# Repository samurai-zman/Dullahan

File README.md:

# Dullahan
A portable "Headless" modular multiport multitool, designed to emphasize adaptability for electronic measurements.

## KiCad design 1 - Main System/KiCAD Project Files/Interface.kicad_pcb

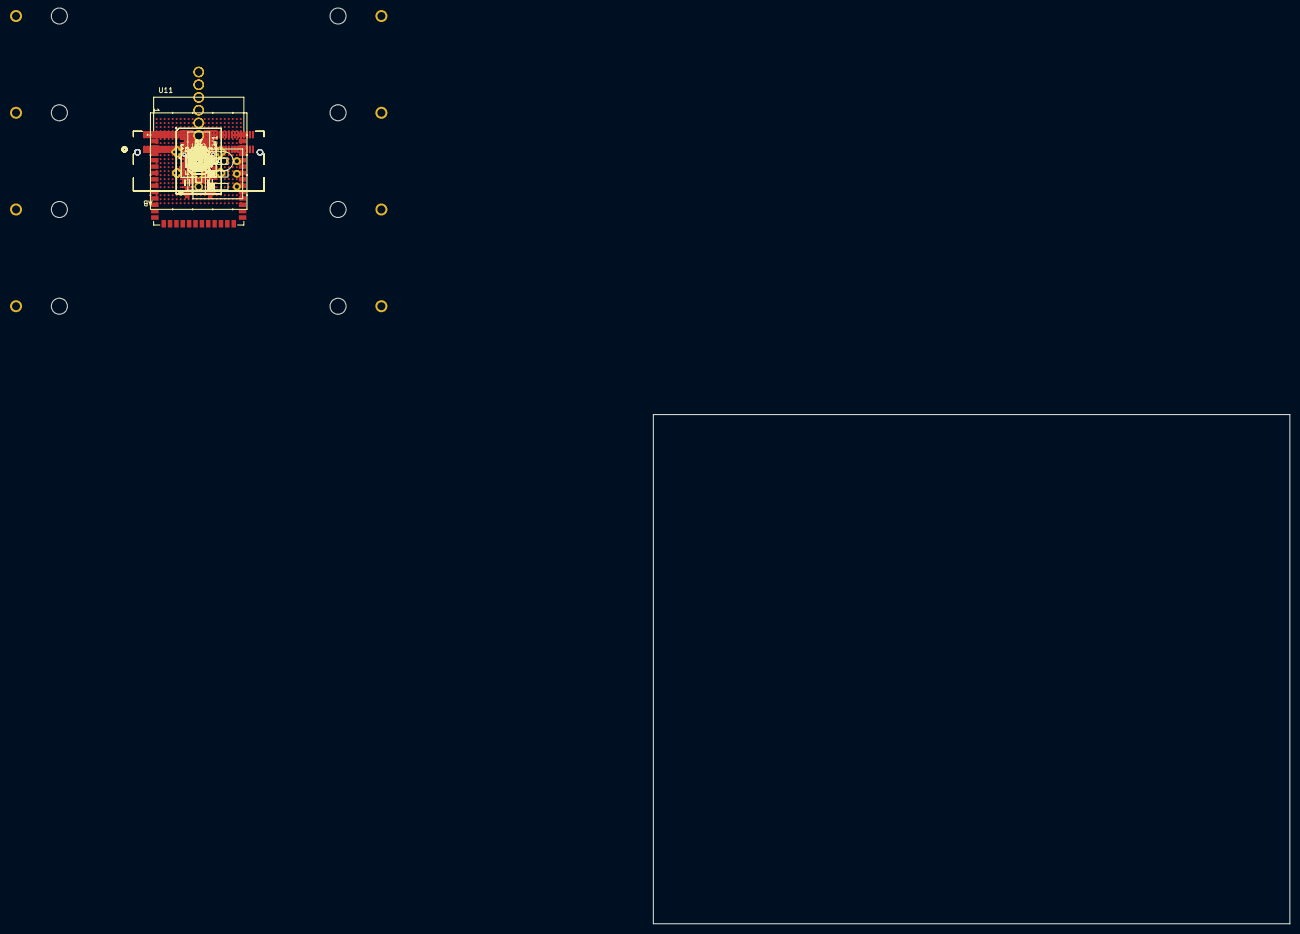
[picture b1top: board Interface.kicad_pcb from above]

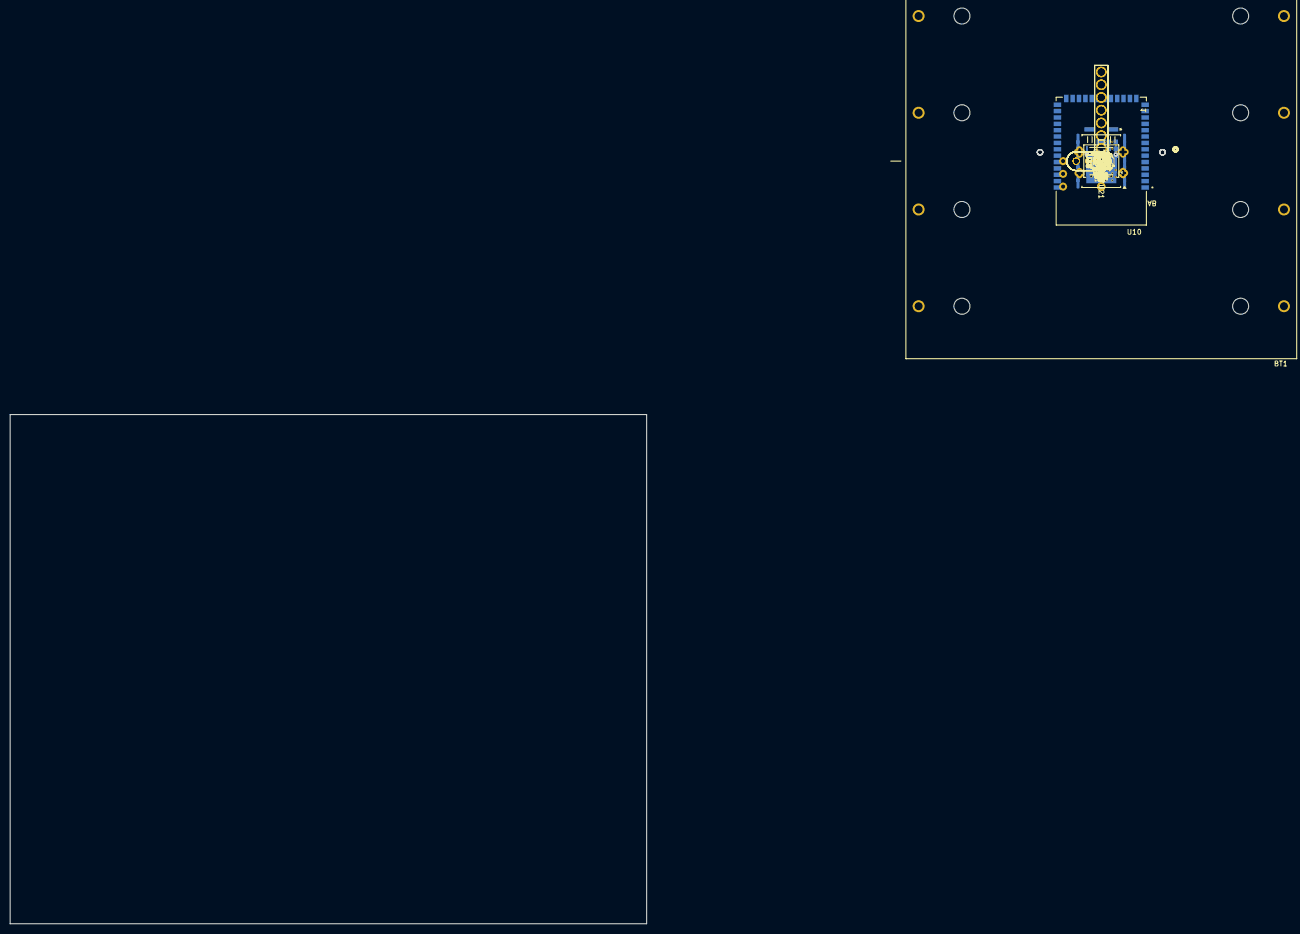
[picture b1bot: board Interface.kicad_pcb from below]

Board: 6 copper layers, 127.0 x 101.6 mm, 580 parts (177 on the bottom side), 365 nets.

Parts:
BT1: BK-18650-PC8; BAT_BK-18650-PC8
C1, C4, C5, C8, C10, C14, C15, C16, C17, C20, C23, C31, C152, C246, C253: 22uF; C_0805
C2, C3, C32, C35, C160, C162, C164, C166, C168, C249: 1uF; C_0805
C6, C7, C11, C12: 220nF; C_0603
C9, C13, C79, C80, C82, C84, C85, C88, C89, C92, C95, C98, C99, C110, C111, C112, C113, C114, C115, C116, C117, C124, C125, C126, C127, C128, C129, C130, C131, C137, C138, C139, C140, C141, C142, C144, C146: 470nF; C_0402
C18: 47pF; C_0805
C19: 18pF; C_0805
C21, C22, C24, C25, C73, C74, C75: 2.2uF; C_0805_2012Metric
C26, C28, C29, C30, C33, C34, C36, C37, C38, C39, C40, C41, C42, C47, C50, C53, C54, C102, C103, C149, C153, C154, C155, C157, C158, C169, C170, C171, C181, C182, C184, C248, C255: 10uF; C_0805
C27: 33pF; C_0805
C43, C44, C45, C46, C59, C60, C61, C62, C183, C240, C241, C245: 100nF; C_0402
C48, C49, C51, C52, C55, C56, C57, C58: 220pF; C_0805
C63, C64, C65, C66, C68, C72, C100, C151, C161, C163, C165, C167, C172, C173, C175, C250: 100nF; C_0805
C67, C69, C70, C71, C174, C176, C177, C178: 1nF; C_0402
C76: 330uF; C_0603
C77, C78, C81, C87, C91, C94, C97, C106, C107, C108, C109, C120, C121, C122, C123, C134, C135, C136, C145: 4.7uF; C_0402
C83, C96, C133, C143: 100uF; C_0603
C86, C90, C93, C104, C105, C118, C119, C132, C147, C148: 47uF; C_0603
C101, C150, C156, C159: 2.2uF; C_0402
C179, C180, C185, C186, C187, C188, C189, C190, C191, C192, C193, C194, C195, C196, C197, C198, C199, C200, C201, C202, C203, C204, C205, C206, C207, C208, C209, C210, C211, C212, C213, C214, C215, C216, C217, C218, C219, C220, C221, C222, C223, C224, C225, C226, C227, C228, C229, C230, C231, C232, C233, C234, C235, C236: 47nF; C_0402
C237, C239: 1uF; C_0402
C238, C242, C243, C244: 10uF; C_0402
C247, C251, C252, C254: 4.7uF; C_0805
D1, D54: PRTR5V0U2X; SOT-143R_Handsoldering
D2, D3, D4, D5, D6, D22, D23, D24, D25, D26, D27, D28, D29, D30, D31, D32, D33, D34, D35, D36, D37, D38, D39, D40, D41, D42, D43, D44, D45, D46, D47, D48, D49, D50, D52, D57, D58, D59, D60, D61, D62, D63, D64, D65, D66, D67: D; D_0805_2012Metric_Pad1.15x1.40mm_HandSolder
D7, D17, D18, D19: BAT60A; D_SOD-323
D8, D9, D10, D11, D12, D13, D14, D20, D21: Blue; LED_0603_1608Metric_Blue
D15: BSTAT; LED_0603
D16: BOK; LED_0603
D51, D53: Blue; D_0805
IC1, IC2, IC3, IC4: AP22966DC8-7; AP22966DC87
IC5: TMUXHS221FRSWR
IC6, IC7: MAX77857CEWB+; BGA35C40P7X5_283X203X69
IC8, IC9: IS43TR16640C-125JBL; BGA96C80P9X16_900X1300X120
J1, J2: Connector, USB-TYPE-C-16P; TYPE-C-SMD_HX-TYPE-C-16PIN
J3: PinSocket_01x03_P2.54mm_Vertical_SMD; PinSocket_1x03_P2.54mm_Vertical
J4, J7, J8, J9: G97R22312HR; CONN_G97R22xx2HR_AMP
J5: JTAGHDR_RPi; PinHeader_01x08_P2.54mm_Vertical_THT_D1.4mm
J6: JTAGHDR_FPGA; PinHeader_01x08_P2.54mm_Vertical_THT_D1.4mm
J17, J18: PinHeader_01x01_P2.54mm_Vertical_THT_D1mm
JP3, JP4: Jumper_2_Bridged; Jumper_2_NC_Trace
L1, L21: 1.5uH; Inductor_4.7x4.7mm
L2, L3, L4, L5: 1.0uH; 0805
L10: 30 Ohm; C_0603_1608Metric
L11: 120 Ohm; C_0603_1608Metric
L12: 0.47uH; Inductor_4.7x4.7mm
Q4: 2N7002; SOT-23
Q5, Q6: T2N7002AK; SOT-23
R1, R2, R4, R8, R37, R38, R42, R43, R44, R82, R83, R84, R85, R86, R87, R115, R116: 10kΩ; R_0402
R3, R6: 510kΩ; R_0402
R5: 200Ω; R_0402
R7: 422Ω; R_0402
R9, R11: 5.1kΩ; R_0805
R10, R18, R35: 1kΩ; R_0805
R12: 5.1Ω; R_0805
R13, R14: 2.2kΩ; R_0805
R15, R16, R119: 10kΩ; R_0805
R17, R19, R23, R59, R124: 12kΩ; R_0402
R20: 47kΩ; R_0805
R21, R22, R25, R28, R29, R30, R45, R118: 330Ω; R_0805
R24, R47, R54, R55, R57, R103, R104, R105: 4.7kΩ; R_0402
R26, R46, R102: 100Ω; R_0402
R27, R39, R40, R41, R71, R74, R80, R81, R98: 0Ω; R_0402
R31, R33, R36: 20kΩ; R_0805
R32: 24kΩ; R_0805
R34: 68kΩ; R_0805
R48, R49, R50, R51, R52, R53, R66, R67, R68, R70, R73, R99, R100, R122: 1kΩ; R_0402
R56: 24.9Ω; R_0402
R58, R77: 510Ω; R_0402
R60, R89, R91, R93, R95, R97, R123: 100kΩ; R_0402
R61, R62, R63, R64, R65, R69, R72: 20kΩ; R_0402
R75, R76, R78, R79: 22Ω; R_0402
R88, R90, R92, R94, R96: 1MΩ; R_0402
R101, R106, R107, R108, R109, R110, R111, R112, R113: 49.9Ω; R_0402
R114, R121: 240Ω; R_0402
R117: 10kΩ; C_0805
R120: 330Ω; C_0805
RV1, RV2, RV3, RV4: CG0402MLU-3.3G; VARC1005X41N
S1, S2, S3, S4, S39, S41: Tactile Button, 160gf; SW_TS-1088-AR02016
S5, S6, S7, S8, S9, S10, S11, S12, S13, S14, S15, S16, S17, S18, S19, S20, S21, S22, S23, S24, S25, S26, S27, S28, S29, S30, S31, S32, S33, S34, S35, S36, S37, S38, S40, S45, S46, S47, S48, S49, S50, S51, S52, S53, S54, S55: Tactile Button, 160gf; SW-SMD_4P-L5.1-W5.1-P3.70-LS6.5-TL-2
SW1: SW_DIP_x03; SW_DIP_SPSTx03_Slide_9.78x9.8mm_W7.62mm_P2.54mm
SW2: SPDT_Slide_PTH_11.6x4.0mm; Slide_SPDT_PTH_11.6x4.0mm
TH1: Thermistor_NTC; R_1206
TP6, TP7: TestPoint_Alt; TestPoint-1.0mm
U1: MAX20029BATIA/V+; 21-0140AK_T2855&plus_5_MXM-L
U2, U4, U5, U6, U8, U9: LD39200PU33R; SON95P300X300X100-7N
U3, U18, U30: STTH1002CB-TR; DPAK_STM-L
U7: ADS7830; TSSOP-16_4.4x5mm_P0.65mm
U10, U11: ESP32-S3-WROOM-1-N4; XCVR_ESP32-S3-WROOM-1-N4
U12, U13, U14, U15, U16, U35, U36, U37: ACS711xEXLT-15AB; Allegro_QFN-12-10-1EP_3x3mm_P0.5mm
U17: XC7Z020-1CLG484C; CLG484_XIL-L
U19: MAX77789EWX+T; 21-100639_W362K2&plus_1_ADI-L
U20, U22, U24, U26, U28: TPS2592xx; VSON-10-1EP_3x3mm_P0.5mm_EP1.65x2.4mm_ThermalVias
U21: PCF8574AT; SOIC-16W_7.5x10.3mm_P1.27mm
U23, U29, U31, U32, U33, U34, U38, U39, U40: DSS1NB32A223Q91A; DSS1NB32A223Q91A_MUR
U25: BD3539FVM-TR; MSOP8_ROM
Y1: ASDMB-xxxMHz; Oscillator_SMD_Abracon_ASDMB-4Pin_2.5x2.0mm

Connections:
+0V675: C203.1, C204.1, C205.1, C206.1, C207.1, C208.1, C209.1, C210.1, C211.1, C212.1, R101.1, R106.1, R107.1, R108.1, R109.1, R110.1, R111.1, R112.1, R113.1
+0V675_REF: U17.H7 (PS_DDR_VREF0_502), U17.P7 (PS_DDR_VREF1_502)
+1V0FPGA: C4.1, C5.1, C16.1, C76.1, C77.1, C78.1, C79.1, C80.1, C81.1, C82.1, C83.1, C84.1, C85.1, C133.1, C135.1, C137.1, C139.1, C141.1, L2.1, U1.28 (OUTS1), U17.G8 (VCCPINT), U17.H9 (VCCPINT), U17.H11 (VCCBRAM), U17.J8 (VCCPINT), U17.J10 (VCCBRAM), U17.J12 (VCCINT), U17.J14 (VCCINT), U17.K13 (VCCINT), U17.L8 (VCCPINT), U17.L14 (VCCINT), U17.M13 (VCCINT), U17.N8 (VCCPINT), U17.N14 (VCCINT), U17.P13 (VCCINT), U17.R8 (VCCPINT), U17.R14 (VCCINT)
+1V8FPGA: C19.1, C44.1, C86.1, C87.1, C88.1, C89.1, C93.1, C94.1, C95.1, C99.1, C143.1, C145.1, C146.1, C148.1, L11.2, R17.1, R19.2, R23.2, R36.1, U17.A10 (VCCO_MIO1_501), U17.B13 (VCCO_MIO1_501), U17.D9 (VCCO_MIO1_501), U17.E12 (VCCO_MIO1_501), U17.G9 (VCCBATT_0), U17.K9 (VCCPAUX), U17.K11 (VCCADC_0), U17.L10 (VCCAUX), U17.M9 (VCCPAUX), U17.N10 (VCCAUX), U17.P9 (VCCPAUX), U17.P11 (VCCAUX), U17.R10 (VCCAUX), U17.T9 (VCCPAUX)
+1V35FPGA: C18.1, C104.1, C106.1, C108.1, C110.1, C112.1, C114.1, C116.1, C179.1, C180.1, C185.1, C186.1, C187.1, C188.1, C189.1, C190.1, C191.1, C192.1, C193.1, C194.1, C195.1, C196.1, C197.1, C198.1, C199.1, C200.1, C201.1, C202.1, C214.1, C215.1, C216.1, C217.1, C218.1, C219.1, C220.1, C221.1, C222.1, C223.1, C224.1, C225.1, C226.1, C227.1, C228.1, C229.1, C230.1, C231.1, C232.1, C233.1, C234.1, C236.1, IC8.A1 (VDDQ_1), IC8.A8 (VDDQ_2), IC8.B2 (VDD_1), IC8.C1 (VDDQ_3), IC8.C9 (VDDQ_4), IC8.D2 (VDDQ_5), IC8.D9 (VDD_2), IC8.E9 (VDDQ_6), IC8.F1 (VDDQ_7), IC8.G7 (VDD_3), IC8.H1 (VREFDQ), IC8.H2 (VDDQ_8), IC8.H9 (VDDQ_9), IC8.K2 (VDD_4), IC8.K8 (VDD_5), IC8.N1 (VDD_6), IC8.N9 (VDD_7), IC8.R1 (VDD_8), IC8.R9 (VDD_9), IC9.A1 (VDDQ_1), IC9.A8 (VDDQ_2), IC9.B2 (VDD_1), IC9.C1 (VDDQ_3), IC9.C9 (VDDQ_4), IC9.D2 (VDDQ_5), IC9.D9 (VDD_2), IC9.E9 (VDDQ_6), IC9.F1 (VDDQ_7), IC9.G7 (VDD_3), IC9.H1 (VREFDQ), IC9.H2 (VDDQ_8), IC9.H9 (VDDQ_9), IC9.K2 (VDD_4), IC9.K8 (VDD_5), IC9.N1 (VDD_6), IC9.N9 (VDD_7), IC9.R1 (VDD_8), IC9.R9 (VDD_9), R26.2, R31.1, R46.2, R122.1, U17.E2 (VCCO_DDR_502), U17.F5 (VCCO_DDR_502), U17.H1 (VCCO_DDR_502), U17.J4 (VCCO_DDR_502), U17.K7 (VCCO_DDR_502), U17.M3 (VCCO_DDR_502), U17.N6 (VCCO_DDR_502), U17.R2 (VCCO_DDR_502), U17.V1 (VCCO_DDR_502)
+3V3FPGA: C27.1, C90.1, C91.1, C92.1, C105.1, C107.1, C109.1, C111.1, C113.1, C115.1, C117.1, C118.1, C119.1, C120.1, C121.1, C122.1, C123.1, C124.1, C125.1, C126.1, C127.1, C128.1, C129.1, C130.1, C131.1, C132.1, C134.1, C136.1, C138.1, C140.1, C142.1, C144.1, C147.1, J6.8, R21.1, R33.1, R54.2, R55.2, R57.2, R58.1, R62.2, R71.1, R74.2, R77.1, R103.2, R104.2, R105.2, SW1.4, SW1.5, SW1.6, U17.A20 (VCCO_35), U17.AA10 (VCCO_13), U17.AA20 (VCCO_33), U17.AB3 (VCCO_13), U17.AB13 (VCCO_33), U17.B3 (VCCO_MIO0_500), U17.C6 (VCCO_MIO0_500), U17.C16 (VCCO_35), U17.D19 (VCCO_35), U17.E22 (VCCO_35), U17.F15 (VCCO_35), U17.G18 (VCCO_35), U17.H21 (VCCO_35), U17.K17 (VCCO_34), U17.L20 (VCCO_34), U17.N16 (VCCO_34), U17.P19 (VCCO_34), U17.R12 (VCCO_0), U17.R22 (VCCO_34), U17.T5 (VCCO_13), U17.T7 (RSVDVCC1), U17.T8 (RSVDVCC2), U17.T10 (RSVDVCC3), U17.T13 (CFGBVS_0), U17.T15 (VCCO_34), U17.U8 (VCCO_13), U17.U18 (VCCO_33), U17.V11 (VCCO_13), U17.V21 (VCCO_33), U17.W4 (VCCO_13), U17.W14 (VCCO_33), U17.Y7 (VCCO_13), U17.Y17 (VCCO_33), Y1.4 (VDD)
+3V3JTAG: C62.1, C184.1, C237.1, C238.1, J5.8, R45.1, R115.1, R116.2, U8.1 (OUT), U8.2 (SENSE), U10.2 (3V3)
+3V3KEB: C63.1, C248.1, C249.1, C255.1, J17.1 (Pin_1_1), R117.1, R120.1, U9.1 (OUT), U9.2 (SENSE), U11.2 (3V3)
+5VB: R48.2, R49.2, R50.2, R51.2, R52.2, R53.2, R99.2, R100.2
+5VM: C14.1, C15.1, C64.1, C65.1, C66.1, C68.1, C72.1, C172.1, C173.1, C175.1, C242.1, C244.1, D7.2 (A), D17.2 (A), D18.2 (A), D19.2 (A), IC7.D4 (OUT_1), IC7.E1 (FB), IC7.E4 (OUT_2), IC7.E5 (OUT_3), IC7.E6 (OUT_4), R12.2, R13.1, R14.1, R15.1, R16.1, R119.1, U12.10 (VCC), U13.10 (VCC), U14.10 (VCC), U15.10 (VCC), U16.10 (VCC), U21.16 (VDD), U35.10 (VCC), U36.10 (VCC), U37.10 (VCC)
+VIOB: C150.1, R2.1, R82.1, R83.1, U19.F4 (VDD)
+VIOM: C13.1, IC7.A2 (VIO), R8.1, R86.1, R87.1
+VIOPI: C9.1, IC6.A2 (VIO), R4.1, R84.1, R85.1
/3V3 Regulator Supplies/3M1: U37.1 (IP+), U40.3
/3V3 Regulator Supplies/3M2: U36.1 (IP+), U39.3
/3V3 Regulator Supplies/3M3: U35.1 (IP+), U38.3
/3V3 Regulator Supplies/3M4: U16.1 (IP+), U34.3
/3V3 Regulator Supplies/5M1: U15.1 (IP+), U33.3
/3V3 Regulator Supplies/5M2: U14.1 (IP+), U32.3
/3V3 Regulator Supplies/5M3: U13.1 (IP+), U31.3
/3V3 Regulator Supplies/5M4: U12.1 (IP+), U29.3
/3V3 Regulator Supplies/5VM1: C53.1, C160.1, C171.1, IC1.1 (VIN1), IC1.5 (VIN2), R98.1, U20.6 (OUT), U20.7 (OUT), U20.8 (OUT)
/3V3 Regulator Supplies/5VM2: C50.1, C164.1, C170.1, IC2.1 (VIN1), IC2.5 (VIN2), R81.1, U24.6 (OUT), U24.7 (OUT), U24.8 (OUT)
/3V3 Regulator Supplies/5VM3: C47.1, C166.1, C169.1, IC3.1 (VIN1), IC3.5 (VIN2), R80.1, U26.6 (OUT), U26.7 (OUT), U26.8 (OUT)
/3V3 Regulator Supplies/5VM4: C36.1, C54.1, C168.1, IC4.1 (VIN1), IC4.5 (VIN2), R27.1, U28.6 (OUT), U28.7 (OUT), U28.8 (OUT)
/3V3 Regulator Supplies/M1_3VEN: IC1.4 (EN2), U21.5 (P1)
/3V3 Regulator Supplies/M1_5VEN: IC1.2 (EN1), U21.11 (P6)
/3V3 Regulator Supplies/M1_PG: U2.4 (PG), U10.26 (IO45)
/3V3 Regulator Supplies/M2_3VEN: IC2.4 (EN2), U21.7 (P3)
/3V3 Regulator Supplies/M2_5VEN: IC2.2 (EN1), U21.9 (P4)
/3V3 Regulator Supplies/M2_PG: U4.4 (PG), U10.16 (IO46)
/3V3 Regulator Supplies/M3_3VEN: IC3.4 (EN2), U21.10 (P5)
/3V3 Regulator Supplies/M3_5VEN: IC3.2 (EN1), U21.6 (P2)
/3V3 Regulator Supplies/M3_PG: U5.4 (PG), U10.24 (IO47)
/3V3 Regulator Supplies/M4_3VEN: IC4.4 (EN2), U21.12 (P7)
/3V3 Regulator Supplies/M4_5VEN: IC4.2 (EN1), U21.4 (P0)
/3V3 Regulator Supplies/M4_PG: U6.4 (PG), U10.25 (IO48)
/5V Boost Supplies/5VM_INT: IC7.C2 (POKB/_INTB), R87.2, R119.2, U10.23 (IO21), U21.13 (~INT)
/5V Boost Supplies/5VM_SCL: IC7.A1 (SCL), R14.2, R16.2, R86.2, U7.14 (SCL), U10.11 (IO18), U21.15 (SDA)
/5V Boost Supplies/5VM_SDA: IC7.B1 (SDA), R8.2, R13.2, R15.2, U7.15 (SDA), U10.10 (IO17), U21.14 (SCL)
/5V Boost Supplies/5VP_INT: IC6.C2 (POKB/_INTB), R83.2, R84.2, U10.30 (IO37), U19.B1 (INTB)
/5V Boost Supplies/5VP_SCL: IC6.A1 (SCL), R82.2, R85.2, U10.34 (IO41), U19.D1 (SCL)
/5V Boost Supplies/5VP_SDA: IC6.B1 (SDA), R2.2, R4.2, U10.33 (IO40), U19.C1 (SDA)
/FPGA Power Distro/+0V674: C246.1, C247.1, U25.3 (VTTS), U25.8 (VTT)
/FPGA Power Distro/+0V674_REF: C251.1, U25.4 (VREF)
/FPGA Power Distro/FPGA_PG: C75.2, Q4.1 (G), R44.2, R124.1, U1.23 (PG4)
/FPGA/FPGA CFG and PWR/BM1: R65.1, R67.1, SW1.1
/FPGA/FPGA CFG and PWR/BM2: R64.1, R68.1, SW1.2
/FPGA/FPGA CFG and PWR/BM3: R63.1, R66.1, SW1.3
/FPGA/FPGA CFG and PWR/CLK: R56.1, Y1.3 (Out)
/FPGA/FPGA CFG and PWR/DONE: Q6.1 (G), U17.T12 (DONE_0)
/FPGA/FPGA CFG and PWR/FPGA_TCK: J6.3, R79.1, R104.1, RV1.1
/FPGA/FPGA CFG and PWR/FPGA_TDI: J6.1, R75.1, R103.1, RV4.1
/FPGA/FPGA CFG and PWR/FPGA_TDO: J6.2, R76.1, RV3.1
/FPGA/FPGA CFG and PWR/FPGA_TMS: J6.4, R78.1, R105.1, RV2.1
/FPGA/FPGA CFG and PWR/PS_LED: R59.1, R60.2, U17.G6 (PS_MIO0_500)
/FPGA/FPGA CFG and PWR/QBOO_CLK_BM4: R72.2, U17.A4 (PS_MIO6_500)
/FPGA/FPGA CFG and PWR/QBOO_D0_BM3: R69.2, U17.A2 (PS_MIO2_500)
/FPGA/FPGA CFG and PWR/QBOO_D1_BM1: R65.2, U17.F6 (PS_MIO3_500)
/FPGA/FPGA CFG and PWR/QBOO_D2_BM2: R64.2, U17.E4 (PS_MIO4_500)
/FPGA/FPGA CFG and PWR/QBOO_D3_BM0: R63.2, U17.A3 (PS_MIO5_500)
/FPGA/FPGA CFG and PWR/QBOO_VM0: R61.2, U17.D5 (PS_MIO7_500)
/FPGA/FPGA CFG and PWR/QBOO_VM1: R62.1, U17.E5 (PS_MIO8_500)
/FPGA/FPGA CFG and PWR/nINIT: R55.1, U17.T14 (INIT_B_0)
/FPGA/FPGA CFG and PWR/nPROGRAM: R54.1, S1.2 (B), U17.T11 (PROGRAM_B_0)
/FPGA/FPGA CFG and PWR/nSRST: C43.1, J6.5, R17.2, S3.2 (B), U17.C9 (PS_SRST_B_501)
/FPGA/FPGA DDR/DDR_A0: IC8.N3 (A0), IC9.N3 (A0), U17.M4 (PS_DDR_A0_502)
/FPGA/FPGA DDR/DDR_A1: IC8.P7 (A1), IC9.P7 (A1), U17.M5 (PS_DDR_A1_502)
/FPGA/FPGA DDR/DDR_A2: IC8.P3 (A2), IC9.P3 (A2), U17.K4 (PS_DDR_A2_502)
/FPGA/FPGA DDR/DDR_A3: IC8.N2 (A3), IC9.N2 (A3), U17.L4 (PS_DDR_A3_502)
/FPGA/FPGA DDR/DDR_A4: IC8.P8 (A4), IC9.P8 (A4), U17.K6 (PS_DDR_A4_502)
/FPGA/FPGA DDR/DDR_A5: IC8.P2 (A5), IC9.P2 (A5), U17.K5 (PS_DDR_A5_502)
/FPGA/FPGA DDR/DDR_A6: IC8.R8 (A6), IC9.R8 (A6), U17.J7 (PS_DDR_A6_502)
/FPGA/FPGA DDR/DDR_A7: IC8.R2 (A7), IC9.R2 (A7), U17.J6 (PS_DDR_A7_502)
/FPGA/FPGA DDR/DDR_A8: IC8.T8 (A8), IC9.T8 (A8), U17.J5 (PS_DDR_A8_502)
/FPGA/FPGA DDR/DDR_A9: IC8.R3 (A9), IC9.R3 (A9), U17.H5 (PS_DDR_A9_502)
/FPGA/FPGA DDR/DDR_A10: IC8.L7 (A10/AP), IC9.L7 (A10/AP), U17.J3 (PS_DDR_A10_502)
/FPGA/FPGA DDR/DDR_A11: IC8.R7 (A11), IC9.R7 (A11), U17.G5 (PS_DDR_A11_502)
/FPGA/FPGA DDR/DDR_A12: IC8.N7 (A12/BC#), IC9.N7 (A12/BC#), U17.H4 (PS_DDR_A12_502)
/FPGA/FPGA DDR/DDR_A13: IC8.T3 (NC(A13)), IC9.T3 (NC(A13)), U17.F4 (PS_DDR_A13_502)
/FPGA/FPGA DDR/DDR_A14: IC8.T7 (NC(A14)), IC9.T7 (NC(A14)), U17.G4 (PS_DDR_A14_502)
/FPGA/FPGA DDR/DDR_BA0: IC8.M2 (BA0), IC9.M2 (BA0), R111.2, U17.L7 (PS_DDR_BA0_502)
/FPGA/FPGA DDR/DDR_BA1: IC8.N8 (BA1), IC9.N8 (BA1), R112.2, U17.L6 (PS_DDR_BA1_502)
/FPGA/FPGA DDR/DDR_BA2: IC8.M3 (BA2), IC9.M3 (BA2), R113.2, U17.M6 (PS_DDR_BA2_502)
/FPGA/FPGA DDR/DDR_CAS: IC8.K3 (CAS#), IC9.K3 (CAS#), R108.2, U17.P3 (PS_DDR_CAS_B_502)
/FPGA/FPGA DDR/DDR_CKE: IC8.K9 (CKE), IC9.K9 (CKE), R106.2, U17.V3 (PS_DDR_CKE_502)
/FPGA/FPGA DDR/DDR_CKN: IC8.K7 (CK#), IC9.K7 (CK#), R102.1, U17.N5 (PS_DDR_CKN_502)
/FPGA/FPGA DDR/DDR_CKP: IC8.J7 (CK), IC9.J7 (CK), R102.2, U17.N4 (PS_DDR_CKP_502)
/FPGA/FPGA DDR/DDR_CS: IC8.L2 (CS#), IC9.L2 (CS#), R107.2, U17.P6 (PS_DDR_CS_B_502)
/FPGA/FPGA DDR/DDR_DM0: IC8.D3 (DMU), IC9.D3 (DMU), U17.B1 (PS_DDR_DM0_502)
/FPGA/FPGA DDR/DDR_DM1: IC8.E7 (DML), IC9.E7 (DML), U17.H3 (PS_DDR_DM1_502)
/FPGA/FPGA DDR/DDR_ODT: IC8.K1 (ODT), IC9.K1 (ODT), R101.2, U17.P5 (PS_DDR_ODT_502)
/FPGA/FPGA DDR/DDR_RAS: IC8.J3 (RAS#), IC9.J3 (RAS#), R109.2, U17.R5 (PS_DDR_RAS_B_502)
/FPGA/FPGA DDR/DDR_WE: IC8.L3 (WE#), IC9.L3 (WE#), R110.2, U17.R4 (PS_DDR_WE_B_502)
/FPGA/FPGA DDR/DDR_nRST: IC8.T2 (RESET#), IC9.T2 (RESET#), R47.1, U17.F3 (PS_DDR_DRST_B_502)
/FPGA/FPGA DDR/DQSL_N: IC8.G3 (DQSL#), IC9.G3 (DQSL#), U17.J2 (PS_DDR_DQS_N1_502)
/FPGA/FPGA DDR/DQSL_P: IC8.F3 (DQSL), IC9.F3 (DQSL), U17.H2 (PS_DDR_DQS_P1_502)
/FPGA/FPGA DDR/DQSU_N: IC8.B7 (DQSU#), IC9.B7 (DQSU#), U17.D2 (PS_DDR_DQS_N0_502)
/FPGA/FPGA DDR/DQSU_P: IC8.C7 (DQSU), IC9.C7 (DQSU), U17.C2 (PS_DDR_DQS_P0_502)
/Interface/Interface Controller/CC1: J2.A5 (CC1), R9.1
/Interface/Interface Controller/CC2: J2.B5 (CC2), R11.1
/Interface/Interface Controller/COL0: S5.1 (A), S5.2 (B), S15.1 (A), S15.2 (B), S24.1 (A), S24.2 (B), S31.1 (A), S31.2 (B), U11.8 (IO15)
/Interface/Interface Controller/COL1: S6.1 (A), S6.2 (B), S16.1 (A), S16.2 (B), S25.1 (A), S25.2 (B), S32.1 (A), S32.2 (B), U11.9 (IO16)
/Interface/Interface Controller/COL2: S7.1 (A), S7.2 (B), S17.1 (A), S17.2 (B), S26.1 (A), S26.2 (B), S33.1 (A), S33.2 (B), U11.10 (IO17)
/Interface/Interface Controller/COL3: S8.1 (A), S8.2 (B), S18.1 (A), S18.2 (B), S27.1 (A), S27.2 (B), S34.1 (A), S34.2 (B), U11.11 (IO18)
/Interface/Interface Controller/COL4: S9.1 (A), S9.2 (B), S19.1 (A), S19.2 (B), S28.1 (A), S28.2 (B), S35.1 (A), S35.2 (B), U11.15 (IO3)
/Interface/Interface Controller/COL5: S10.1 (A), S10.2 (B), S20.1 (A), S20.2 (B), S29.1 (A), S29.2 (B), U11.16 (IO46)
/Interface/Interface Controller/COL6: S11.1 (A), S11.2 (B), S21.1 (A), S21.2 (B), S30.1 (A), S30.2 (B), U11.17 (IO9)
/Interface/Interface Controller/COL7: S12.1 (A), S12.2 (B), S22.1 (A), S22.2 (B), S36.1 (A), S36.2 (B), U11.18 (IO10)
/Interface/Interface Controller/COL8: S13.1 (A), S13.2 (B), S23.1 (A), S23.2 (B), S37.1 (A), S37.2 (B), U11.19 (IO11)
/Interface/Interface Controller/COL9: S14.1 (A), S14.2 (B), S38.1 (A), S38.2 (B), S40.1 (A), S40.2 (B), U11.20 (IO12)
/Interface/Interface Controller/COL10: S45.1 (A), S45.2 (B), S46.1 (A), S46.2 (B), S47.1 (A), S47.2 (B), U11.21 (IO13)
/Interface/Interface Controller/COL11: S48.1 (A), S48.2 (B), S49.1 (A), S49.2 (B), S50.1 (A), S50.2 (B), U11.22 (IO14)
/Interface/Interface Controller/COL12: S51.1 (A), S51.2 (B), S54.1 (A), S54.2 (B), S55.1 (A), S55.2 (B), U11.23 (IO21)
/Interface/Interface Controller/COL13: S52.1 (A), S52.2 (B), U11.24 (IO47)
/Interface/Interface Controller/COL14: S53.1 (A), S53.2 (B), U11.25 (IO48)
/Interface/Interface Controller/ROW0: D2.1 (K), D3.1 (K), D4.1 (K), D5.1 (K), D6.1 (K), D22.1 (K), D23.1 (K), D24.1 (K), D25.1 (K), D26.1 (K), D57.1 (K), D61.1 (K), D63.1 (K), D64.1 (K), D65.1 (K), U11.30 (IO37)
/Interface/Interface Controller/ROW1: D27.1 (K), D28.1 (K), D29.1 (K), D30.1 (K), D31.1 (K), D32.1 (K), D33.1 (K), D34.1 (K), D35.1 (K), D52.1 (K), D58.1 (K), D60.1 (K), D66.1 (K), U11.31 (IO38)
/Interface/Interface Controller/ROW2: D36.1 (K), D37.1 (K), D38.1 (K), D39.1 (K), D40.1 (K), D41.1 (K), D42.1 (K), D48.1 (K), D49.1 (K), D50.1 (K), D59.1 (K), D62.1 (K), D67.1 (K), U11.32 (IO39)
/Interface/Interface Controller/ROW3: D43.1 (K), D44.1 (K), D45.1 (K), D46.1 (K), D47.1 (K), U11.35 (IO42)
/Interface/Interface Controller/RUSB_N: D54.3 (I/O2), J2.A7 (D-), J2.B7 (D-), U11.13 (IO19)
/Interface/Interface Controller/RUSB_P: D54.2 (I/O1), J2.A6 (D+), J2.B6 (D+), U11.14 (IO20)
/Interface/Interface Controller/eBOOT: S39.2 (B), U11.27 (IO0)
/Interface/Interface Controller/nERST: R117.2, S41.2 (B), U11.3 (EN)
/JTAG&Monitor/FPGA_TCK: J5.3, U10.31 (IO38)
/JTAG&Monitor/FPGA_TDI: J5.1, U10.22 (IO14)
/JTAG&Monitor/FPGA_TDO: J5.2, U10.35 (IO42)
/JTAG&Monitor/FPGA_TMS: J5.4, U10.32 (IO39)
/JTAG&Monitor/RUSB_N: IC5.4 (DA-), U10.13 (IO19)
/JTAG&Monitor/RUSB_P: IC5.5 (DA+), U10.14 (IO20)
/JTAG&Monitor/eBOOT: S2.2 (B), U10.27 (IO0)
/JTAG&Monitor/nERST: C239.1, R115.2, R116.1, S4.2 (B), U10.3 (EN)
/Module Monitoring/I3_M1: C46.2, C178.1, U7.2 (CH1), U37.9 (VIOUT)
/Module Monitoring/I3_M2: C60.2, C177.1, U7.4 (CH3), U36.9 (VIOUT)
/Module Monitoring/I3_M3: C176.1, C183.2, U7.6 (CH5), U35.9 (VIOUT)
/Module Monitoring/I3_M4: C174.1, C241.2, U7.8 (CH7), U16.9 (VIOUT)
/Module Monitoring/I5_M1: C45.2, C71.1, U7.1 (CH0), U15.9 (VIOUT)
/Module Monitoring/I5_M2: C59.2, C70.1, U7.3 (CH2), U14.9 (VIOUT)
/Module Monitoring/I5_M3: C61.2, C69.1, U7.5 (CH4), U13.9 (VIOUT)
/Module Monitoring/I5_M4: C67.1, C240.2, U7.7 (CH6), U12.9 (VIOUT)
/USB and Battery Management/CC1: J1.A5 (CC1), U19.F1 (CC1)
/USB and Battery Management/CC2: J1.B5 (CC2), U19.E1 (CC2)
/USB and Battery Management/STAT2: SW2.3 (C), U19.E2 (STAT2)
/USB and Battery Management/USB_DN: D1.3 (I/O2), IC5.2 (D-), J1.A7 (D-), J1.B7 (D-)
/USB and Battery Management/USB_DP: D1.2 (I/O1), IC5.1 (D+), J1.A6 (D+), J1.B6 (D+)
/USB and Battery Management/VBAT+: BT1.1+, BT1.2+, BT1.3+, BT1.4+, C102.1, J3.1, U19.E4 (BAT), U19.E5 (BAT), U19.E6 (BAT)
/USB and Battery Management/Vpvl: JP3.2 (B), R1.1
GNDA: C45.1, C46.1, C59.1, C60.1, C61.1, C148.2, C183.1, C240.1, C241.1, C245.2, C250.2, J4.A37, J7.A37, J8.A37, J9.A37, U17.K12 (GNDADC_0), Y1.2 (GND)
GNDD: BT1.1-, BT1.2-, BT1.3-, BT1.4-, C1.2, C2.2, C3.2, C4.2, C5.2, C8.2, C9.2, C10.2, C13.2, C14.2, C15.2, C16.2, C17.2, C20.2, C21.1, C22.2, C23.2, C25.2, C26.2, C28.2, C29.2, C30.2, C31.2, C32.2, C33.2, C34.2, C35.2, C36.2, C37.2, C38.2, C39.2, C40.2, C41.2, C42.2, C43.2, C44.2, C47.2, C48.2, C49.2, C50.2, C51.2, C52.2, C53.2, C54.2, C55.2, C56.2, C57.2, C58.2, C62.2, C63.2, C64.2, C65.2, C66.2, C67.2, C68.2, C69.2, C70.2, C71.2, C72.2, C76.2, C77.2, C78.2, C79.2, C80.2, C81.2, C82.2, C83.2, C84.2, C85.2, C86.2, C87.2, C88.2, C89.2, C90.2, C91.2, C92.2, C93.2, C94.2, C95.2, C96.2, C97.2, C98.2, C99.2, C100.2, C101.2, C102.2, C103.2, C104.2, C105.2, C106.2, C107.2, C108.2, C109.2, C110.2, C111.2, C112.2, C113.2, C114.2, C115.2, C116.2, C117.2, C118.2, C119.2, C120.2, C121.2, C122.2, C123.2, C124.2, C125.2, C126.2, C127.2, C128.2, C129.2, C130.2, C131.2, C132.2, C133.2, C134.2, C135.2, C136.2, C137.2, C138.2, C139.2, C140.2, C141.2, C142.2, C143.2, C144.2, C145.2, C146.2, C147.2, C149.2, C150.2, C152.2, C153.2, C154.2, C155.2, C156.2, C157.2, C158.2, C159.2, C160.2, C161.2, C162.2, C163.2, C164.2, C165.2, C166.2, C167.2, C168.2, C169.2, C170.2, C171.2, C172.2, C173.2, C174.2, C175.2, C176.2, C177.2, C178.2, C179.2, C180.2, C181.2, C182.2, C184.2, C185.2, C186.2, C187.2, C188.2, C189.2, C190.2, C191.2, C192.2, C193.2, C194.2, C195.2, C196.2, C197.2, C198.2, C199.2, C200.2, C201.2, C202.2, C203.2, C204.2, C205.2, C206.2, C207.2, C208.2, C209.2, C210.2, C211.2, C212.2, C213.2, C215.2, C216.2, C217.2, C218.2, C219.2, C220.2, C221.2, C222.2, C223.2, C224.2, C225.2, C226.2, C227.2, C228.2, C229.2, C230.2, C231.2, C232.2, C233.2, C234.2, C235.2, C237.2, C238.2, C239.2, C242.2, C243.2, C244.2, C246.2, C247.2, C248.2, C249.2, C251.2, C252.2, C253.2, C254.2, C255.2, D1.1 (GND), D9.1 (K), D10.1 (K), D11.1 (K), D12.1 (K), D20.1 (K), D21.1 (K), D51.1 (K), D53.1 (K), D54.1 (GND), IC1.8 (GND), IC1.11 (EP), IC2.8 (GND), IC2.11 (EP), IC3.8 (GND), IC3.11 (EP), IC4.8 (GND), IC4.11 (EP), IC5.3 (GND), IC6.C3 (PGND_1), IC6.C4 (PGND_2), IC6.C5 (PGND_3), IC6.C6 (PGND_4), IC6.C7 (PGND_5), IC6.D2 (PGND_6), IC6.D3 (PGND_7), IC6.E2 (AGND), IC7.C3 (PGND_1), IC7.C4 (PGND_2), IC7.C5 (PGND_3), IC7.C6 (PGND_4), IC7.C7 (PGND_5), IC7.D2 (PGND_6), IC7.D3 (PGND_7), IC7.E2 (AGND), IC8.A9 (VSS_1), IC8.B3 (VSS_2), IC8.E1 (VSS_3), IC8.G8 (VSS_4), IC8.J2 (VSS_5), IC8.J8 (VSS_6), IC8.M1 (VSS_7), IC8.M9 (VSS_8), IC8.P1 (VSS_9), IC8.P9 (VSS_10), IC8.T1 (VSS_11), IC8.T9 (VSS_12), IC9.A9 (VSS_1), IC9.B3 (VSS_2), IC9.E1 (VSS_3), IC9.G8 (VSS_4), IC9.J2 (VSS_5), IC9.J8 (VSS_6), IC9.M1 (VSS_7), IC9.M9 (VSS_8), IC9.P1 (VSS_9), IC9.P9 (VSS_10), IC9.T1 (VSS_11), IC9.T9 (VSS_12), J1.A8 (SBU1), J1.A12B1 (GND), J1.B8 (SBU2), J1.B12A1 (GND), J1.S1 (SHIELD), J2.A8 (SBU1), J2.A12B1 (GND), J2.B8 (SBU2), J2.B12A1 (GND), J2.S1 (SHIELD), J4.A1, J4.A3, J4.A6, J5.7, J6.7, J7.A1, J7.A3, J7.A6, J8.A1, J8.A3, J8.A6, J9.A1, J9.A3, J9.A6, JP4.2 (B), Q4.2 (S), Q5.2 (S), Q6.2 (S), R5.2, R7.2, R9.2, R11.2, R20.2, R23.1, R24.2, R34.1, R35.1, R47.2, R60.1, R61.1, R66.2, R67.2, R68.2, R70.2, R73.2, R89.2, R91.2, R93.2, R95.2, R97.2, R114.1, R121.1, R123.2, RV1.2, RV2.2, RV3.2, RV4.2, S1.1 (A), S2.1 (A), S3.1 (A), S4.1 (A), S39.1 (A), S41.1 (A), TH1.2, U1.4 (PGND1), U1.5 (PGND2), U1.11 (GND), U1.17 (PGND3), U1.18 (PGND4), U1.24 (GND), U1.25 (SYNC), U1.29 (EPAD), U2.3 (GND), U2.7 (EXP), U4.3 (GND), U4.7 (EXP), U5.3 (GND), U5.7 (EXP), U6.3 (GND), U6.7 (EXP), U7.9 (GND), U7.12 (A0), U7.13 (A1), U8.3 (GND), U8.7 (EXP), U9.3 (GND), U9.7 (EXP), U10.1 (GND), U10.40 (GND__1), U10.41_1 (GND__2), U10.41_2 (GND__3), U10.41_3 (GND__4), U10.41_4 (GND__5), U10.41_5 (GND__6), U10.41_6 (GND__7), U10.41_7 (GND__8), U10.41_8 (GND__9), U10.41_9 (GND__10), U11.1 (GND), U11.40 (GND__1), U11.41_1 (GND__2), U11.41_2 (GND__3), U11.41_3 (GND__4), U11.41_4 (GND__5), U11.41_5 (GND__6)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
unnamed: C151.2, L12.2, U19.A4 (LX), U19.A5 (LX), U19.B4 (LX), U19.B5 (LX)
unnamed: C152.1, C153.1, U19.A3 (BYP), U19.B3 (BYP), U19.C3 (BYP)
unnamed: C162.1, U22.6 (OUT), U22.7 (OUT), U22.8 (OUT), U23.1
unnamed: D2.2 (A), S5.4 (D)
unnamed: D3.2 (A), S6.4 (D)
unnamed: D4.2 (A), S7.4 (D)
unnamed: D5.2 (A), S8.4 (D)
unnamed: D6.2 (A), S9.4 (D)
unnamed: C167.1, D7.1 (K), R96.1, U28.3 (VIN), U28.4 (VIN), U28.5 (VIN)
unnamed: D8.2 (A), R21.2
unnamed: D8.1 (K), Q4.3 (D)
unnamed: D9.2 (A), R22.2
unnamed: D10.2 (A), R25.2
unnamed: D11.2 (A), R28.2
unnamed: D12.2 (A), R29.2
unnamed: D13.2 (A), R58.2
unnamed: D13.1 (K), Q5.3 (D)
unnamed: D14.2 (A), R77.2
unnamed: D14.1 (K), Q6.3 (D)
unnamed: D15.1 (K), R10.2
unnamed: D16.1 (K), R18.2
unnamed: C165.1, D17.1 (K), R94.1, U26.3 (VIN), U26.4 (VIN), U26.5 (VIN)
unnamed: C163.1, D18.1 (K), R92.1, U24.3 (VIN), U24.4 (VIN), U24.5 (VIN)
unnamed: C100.1, D19.1 (K), R88.1, U20.3 (VIN), U20.4 (VIN), U20.5 (VIN)
unnamed: D20.2 (A), R30.2
unnamed: D21.2 (A), R45.2
unnamed: D22.2 (A), S10.4 (D)
unnamed: D23.2 (A), S11.4 (D)
unnamed: D24.2 (A), S12.4 (D)
unnamed: D25.2 (A), S13.4 (D)
unnamed: D26.2 (A), S14.4 (D)
unnamed: D27.2 (A), S15.4 (D)
unnamed: D28.2 (A), S16.4 (D)
unnamed: D29.2 (A), S17.4 (D)
unnamed: D30.2 (A), S18.4 (D)
unnamed: D31.2 (A), S19.4 (D)
unnamed: D32.2 (A), S20.4 (D)
unnamed: D33.2 (A), S21.4 (D)
unnamed: D34.2 (A), S22.4 (D)
unnamed: D35.2 (A), S23.4 (D)
unnamed: D36.2 (A), S24.4 (D)
unnamed: D37.2 (A), S25.4 (D)
unnamed: D38.2 (A), S26.4 (D)
unnamed: D39.2 (A), S27.4 (D)
unnamed: D40.2 (A), S28.4 (D)
unnamed: D41.2 (A), S29.4 (D)
unnamed: D42.2 (A), S30.4 (D)
unnamed: D43.2 (A), S31.4 (D)
unnamed: D44.2 (A), S32.4 (D)
unnamed: D45.2 (A), S33.4 (D)
unnamed: D46.2 (A), S34.4 (D)
unnamed: D47.2 (A), S35.4 (D)
unnamed: D48.2 (A), S36.4 (D)
unnamed: D49.2 (A), S37.4 (D)
unnamed: D50.2 (A), S38.4 (D)
unnamed: D51.2 (A), R118.2
unnamed: D52.2 (A), S40.4 (D)
unnamed: D53.2 (A), R120.2
unnamed: D57.2 (A), S45.4 (D)
unnamed: D58.2 (A), S46.4 (D)
unnamed: D59.2 (A), S47.4 (D)
unnamed: D60.2 (A), S48.4 (D)
unnamed: D61.2 (A), S49.4 (D)
unnamed: D62.2 (A), S50.4 (D)
unnamed: D63.2 (A), S51.4 (D)
unnamed: D64.2 (A), S52.4 (D)
unnamed: D65.2 (A), S53.4 (D)
unnamed: D66.2 (A), S54.4 (D)
unnamed: D67.2 (A), S55.4 (D)
unnamed: C49.1, IC1.9 (SS1)
unnamed: C48.1, IC1.7 (SS2)
unnamed: IC1.3 (VBIAS), R98.2
unnamed: C30.1, IC1.10 (VOUT1), U33.1
unnamed: C26.1, IC1.6 (VOUT2), U2.5 (EN), U2.6 (IN)
unnamed: C51.1, IC2.9 (SS1)
unnamed: C52.1, IC2.7 (SS2)
unnamed: IC2.3 (VBIAS), R81.2
unnamed: C33.1, IC2.10 (VOUT1), U32.1
unnamed: C28.1, IC2.6 (VOUT2), U4.5 (EN), U4.6 (IN)
unnamed: C55.1, IC3.9 (SS1)
unnamed: C56.1, IC3.7 (SS2)
unnamed: IC3.3 (VBIAS), R80.2
unnamed: C37.1, IC3.10 (VOUT1), U31.1
unnamed: C38.1, IC3.6 (VOUT2), U5.5 (EN), U5.6 (IN)
unnamed: C57.1, IC4.9 (SS1)
unnamed: C58.1, IC4.7 (SS2)
unnamed: IC4.3 (VBIAS), R27.2
unnamed: C39.1, IC4.10 (VOUT1), U29.1
unnamed: C40.1, IC4.6 (VOUT2), U6.5 (EN), U6.6 (IN)
unnamed: IC5.7 (DB+), U19.F2 (DP)
unnamed: IC5.6 (DB-), U19.F3 (DN)
unnamed: IC5.8 (OEN), JP4.1 (A)
unnamed: IC5.10 (SEL), R24.1, SW2.2 (B)
unnamed: C6.2, IC6.A3 (BST1)
unnamed: C7.1, IC6.E3 (BST2)
unnamed: IC6.B2 (EN_1), IC6.B3 (EN_2), IC6.B4 (IN_4), R3.2
unnamed: C8.1, C10.1, C161.1, IC6.D4 (OUT_1), IC6.E1 (FB), IC6.E4 (OUT_2), IC6.E5 (OUT_3), IC6.E6 (OUT_4), R90.1, U22.3 (VIN), U22.4 (VIN), U22.5 (VIN)
unnamed: C154.1, C155.1, IC6.A4 (IN_1), IC6.A5 (IN_2), IC6.A6 (IN_3), R3.1, U3.3
unnamed: C6.1, IC6.A7 (LX1_1), IC6.B5 (LX1_2), IC6.B6 (LX1_3), IC6.B7 (LX1_4), L1.1
unnamed: C7.2, IC6.D5 (LX2_1), IC6.D6 (LX2_2), IC6.D7 (LX2_3), IC6.E7 (LX2_4), L1.2
unnamed: IC6.D1 (SEL), R5.1
unnamed: C156.1, IC6.C1 (VL)
unnamed: C11.2, IC7.A3 (BST1)
unnamed: C12.1, IC7.E3 (BST2)
unnamed: IC7.B2 (EN_1), IC7.B3 (EN_2), IC7.B4 (IN_4), R6.2
unnamed: C157.1, C158.1, IC7.A4 (IN_1), IC7.A5 (IN_2), IC7.A6 (IN_3), R6.1, U18.3
unnamed: C11.1, IC7.A7 (LX1_1), IC7.B5 (LX1_2), IC7.B6 (LX1_3), IC7.B7 (LX1_4), L21.1
unnamed: C12.2, IC7.D5 (LX2_1), IC7.D6 (LX2_2), IC7.D7 (LX2_3), IC7.E7 (LX2_4), L21.2
unnamed: IC7.D1 (SEL), R7.1
unnamed: C159.1, IC7.C1 (VL)
unnamed: IC8.E3 (DQL0), U17.K3 (PS_DDR_DQ15_502)
unnamed: IC8.F7 (DQL1), U17.J1 (PS_DDR_DQ14_502)
unnamed: IC8.F2 (DQL2), U17.K1 (PS_DDR_DQ13_502)
unnamed: IC8.F8 (DQL3), U17.L3 (PS_DDR_DQ12_502)
unnamed: IC8.H3 (DQL4), U17.L2 (PS_DDR_DQ11_502)
unnamed: IC8.H8 (DQL5), U17.L1 (PS_DDR_DQ10_502)
unnamed: IC8.G2 (DQL6), U17.G1 (PS_DDR_DQ9_502)
unnamed: IC8.H7 (DQL7), U17.G2 (PS_DDR_DQ8_502)
unnamed: IC8.D7 (DQU0), U17.F1 (PS_DDR_DQ7_502)
unnamed: IC8.C3 (DQU1), U17.F2 (PS_DDR_DQ6_502)
unnamed: IC8.C8 (DQU2), U17.E1 (PS_DDR_DQ5_502)
unnamed: IC8.C2 (DQU3), U17.E3 (PS_DDR_DQ4_502)
unnamed: IC8.A7 (DQU4), U17.D3 (PS_DDR_DQ3_502)
unnamed: IC8.A2 (DQU5), U17.B2 (PS_DDR_DQ2_502)
unnamed: IC8.B8 (DQU6), U17.C3 (PS_DDR_DQ1_502)
unnamed: IC8.A3 (DQU7), U17.D1 (PS_DDR_DQ0_502)
unnamed: C213.1, C214.2, IC8.M8 (VREFCA)
unnamed: IC8.B1 (VSSQ_1), IC8.B9 (VSSQ_2), IC8.D1 (VSSQ_3), IC8.D8 (VSSQ_4), IC8.E2 (VSSQ_5), IC8.E8 (VSSQ_6), IC8.F9 (VSSQ_7), IC8.G1 (VSSQ_8), IC8.G9 (VSSQ_9), IC9.B1 (VSSQ_1), IC9.B9 (VSSQ_2), IC9.D1 (VSSQ_3), IC9.D8 (VSSQ_4), IC9.E2 (VSSQ_5), IC9.E8 (VSSQ_6), IC9.F9 (VSSQ_7), IC9.G1 (VSSQ_8), IC9.G9 (VSSQ_9)
unnamed: IC8.L8 (ZQ), R121.2
unnamed: IC9.E3 (DQL0), U17.Y1 (PS_DDR_DQ31_502)
unnamed: IC9.F7 (DQL1), U17.W3 (PS_DDR_DQ30_502)
unnamed: IC9.F2 (DQL2), U17.Y3 (PS_DDR_DQ29_502)
unnamed: IC9.F8 (DQL3), U17.W1 (PS_DDR_DQ28_502)
unnamed: IC9.H3 (DQL4), U17.U2 (PS_DDR_DQ27_502)
unnamed: IC9.H8 (DQL5), U17.AA1 (PS_DDR_DQ26_502)
unnamed: IC9.G2 (DQL6), U17.U1 (PS_DDR_DQ25_502)
unnamed: IC9.H7 (DQL7), U17.AA3 (PS_DDR_DQ24_502)
unnamed: IC9.D7 (DQU0), U17.R1 (PS_DDR_DQ23_502)
unnamed: IC9.C3 (DQU1), U17.M2 (PS_DDR_DQ22_502)
unnamed: IC9.C8 (DQU2), U17.T2 (PS_DDR_DQ21_502)
unnamed: IC9.C2 (DQU3), U17.R3 (PS_DDR_DQ20_502)
unnamed: IC9.A7 (DQU4), U17.T1 (PS_DDR_DQ19_502)
unnamed: IC9.A2 (DQU5), U17.N3 (PS_DDR_DQ18_502)
unnamed: IC9.B8 (DQU6), U17.T3 (PS_DDR_DQ17_502)
unnamed: IC9.A3 (DQU7), U17.M1 (PS_DDR_DQ16_502)
unnamed: C235.1, C236.2, IC9.M8 (VREFCA)
unnamed: IC9.L8 (ZQ), R114.2
unnamed: J3.2, U19.D3 (EXTSM)
unnamed: C101.1, JP3.1 (A), U19.C6 (PVL)
unnamed: Q5.1 (G), R59.2
unnamed: R32.2, R35.2
unnamed: R69.1, R70.1, R71.2
unnamed: R72.1, R73.1, R74.1
unnamed: R37.2, U1.1 (EN1)
unnamed: R39.2, U1.9 (EN2)
unnamed: R40.2, U1.13 (EN3)
unnamed: R41.2, U1.21 (EN4)
unnamed: L2.2, U1.3 (LX1)
unnamed: L3.2, U1.6 (LX2)
unnamed: L4.2, U1.16 (LX3)
unnamed: L5.2, U1.19 (LX4)
unnamed: C17.1, C19.2, L3.1, R32.1, R36.2, U1.8 (OUTS2)
unnamed: C20.1, C27.2, L4.1, R20.1, R33.2, U1.14 (OUTS3)
unnamed: C18.2, C23.1, L5.1, R31.2, R34.2, U1.22 (OUTS4)
unnamed: C24.2, R38.2, R39.1, U1.27 (PG1)
unnamed: C73.2, R40.1, R42.2, U1.10 (PG2)
unnamed: C74.2, R41.1, R43.2, U1.12 (PG3)
unnamed: C22.1, C24.1, C25.1, C73.1, C74.1, C75.1, L10.1, R37.1, R38.1, R42.1, R43.1, R44.1, U1.2 (PV1), U1.7 (PV2), U1.15 (PV3), U1.20 (PV4), U30.3
unnamed: C21.2, L10.2, U1.26 (VA)
unnamed: C29.1, R22.1, U2.1 (OUT), U2.2 (SENSE), U40.1
unnamed: C34.1, R25.1, U4.1 (OUT), U4.2 (SENSE), U39.1
unnamed: C41.1, R28.1, U5.1 (OUT), U5.2 (SENSE), U38.1
unnamed: C42.1, R29.1, U6.1 (OUT), U6.2 (SENSE), U34.1
unnamed: C245.1, U7.10 (REFin/REFout)
unnamed: C243.1, R12.1, U7.16 (VDD)
unnamed: TP6.1 (1_1), U8.4 (PG)
unnamed: TP7.1 (1_1), U9.4 (PG)
unnamed: R30.1, U10.21 (IO13)
unnamed: R118.1, U11.4 (IO4)
unnamed: R48.1, U12.4 (~FAULT)
unnamed: R49.1, U13.4 (~FAULT)
unnamed: R50.1, U14.4 (~FAULT)
unnamed: R51.1, U15.4 (~FAULT)
unnamed: R52.1, U16.4 (~FAULT)
unnamed: R46.1, U17.M7 (PS_DDR_VRN_502)
unnamed: R26.1, U17.N7 (PS_DDR_VRP_502)
unnamed: R56.2, U17.F7 (PS_CLK_500)
unnamed: R19.1, U17.F8 (PS_MIO_VREF_501)
unnamed: R79.2, U17.G11 (TCK_0)
unnamed: R75.2, U17.H13 (TDI_0)
unnamed: R76.2, U17.G14 (TDO_0)
unnamed: R78.2, U17.G12 (TMS_0)
unnamed: C96.1, C97.1, C98.1, L11.1, U17.H10 (VCCPLL)
unnamed: C151.1, U19.A1 (BST)
unnamed: R18.1, U19.D2 (INOKB)
unnamed: R10.1, U19.C4 (STAT1)
unnamed: R1.2, TH1.1, U19.F6 (THM)
unnamed: R88.2, U20.2 (EN/UVLO)
unnamed: R89.1, U20.10 (ILIM)
unnamed: R90.2, U22.2 (EN/UVLO)
unnamed: R91.1, U22.10 (ILIM)
unnamed: R92.2, U24.2 (EN/UVLO)
unnamed: R93.1, U24.10 (ILIM)
unnamed: R123.1, R124.2, U25.2 (EN)
unnamed: C252.1, R122.2, U25.5 (VDDQ)
unnamed: R94.2, U26.2 (EN/UVLO)
unnamed: R95.1, U26.10 (ILIM)
unnamed: R96.2, U28.2 (EN/UVLO)
unnamed: R97.1, U28.10 (ILIM)
unnamed: R53.1, U35.4 (~FAULT)
unnamed: R99.1, U36.4 (~FAULT)
unnamed: R100.1, U37.4 (~FAULT)
unnamed: R57.1, Y1.1 (Standby)
VBUS: C1.1, C2.1, C3.1, J1.A9B4 (VBUS), J1.B9A4 (VBUS), U19.A2 (CHGIN), U19.B2 (CHGIN), U19.C2 (CHGIN)
VKEB: C31.1, C32.1, C35.1, C182.1, D54.4 (VCC), J2.A9B4 (VBUS), J2.B9A4 (VBUS), J18.1 (Pin_1_1), U9.5 (EN), U9.6 (IN)
VSYS: C103.1, C149.1, C181.1, C253.1, C254.1, D1.4 (VCC), D15.2 (A), D16.2 (A), IC5.9 (VCC), L12.1, U3.1, U3.2, U8.5 (EN), U8.6 (IN), U18.1, U18.2, U19.D4 (SYS), U19.D5 (SYS), U19.D6 (SYS), U25.6 (VCC), U25.7 (VTT_IN), U30.1, U30.2

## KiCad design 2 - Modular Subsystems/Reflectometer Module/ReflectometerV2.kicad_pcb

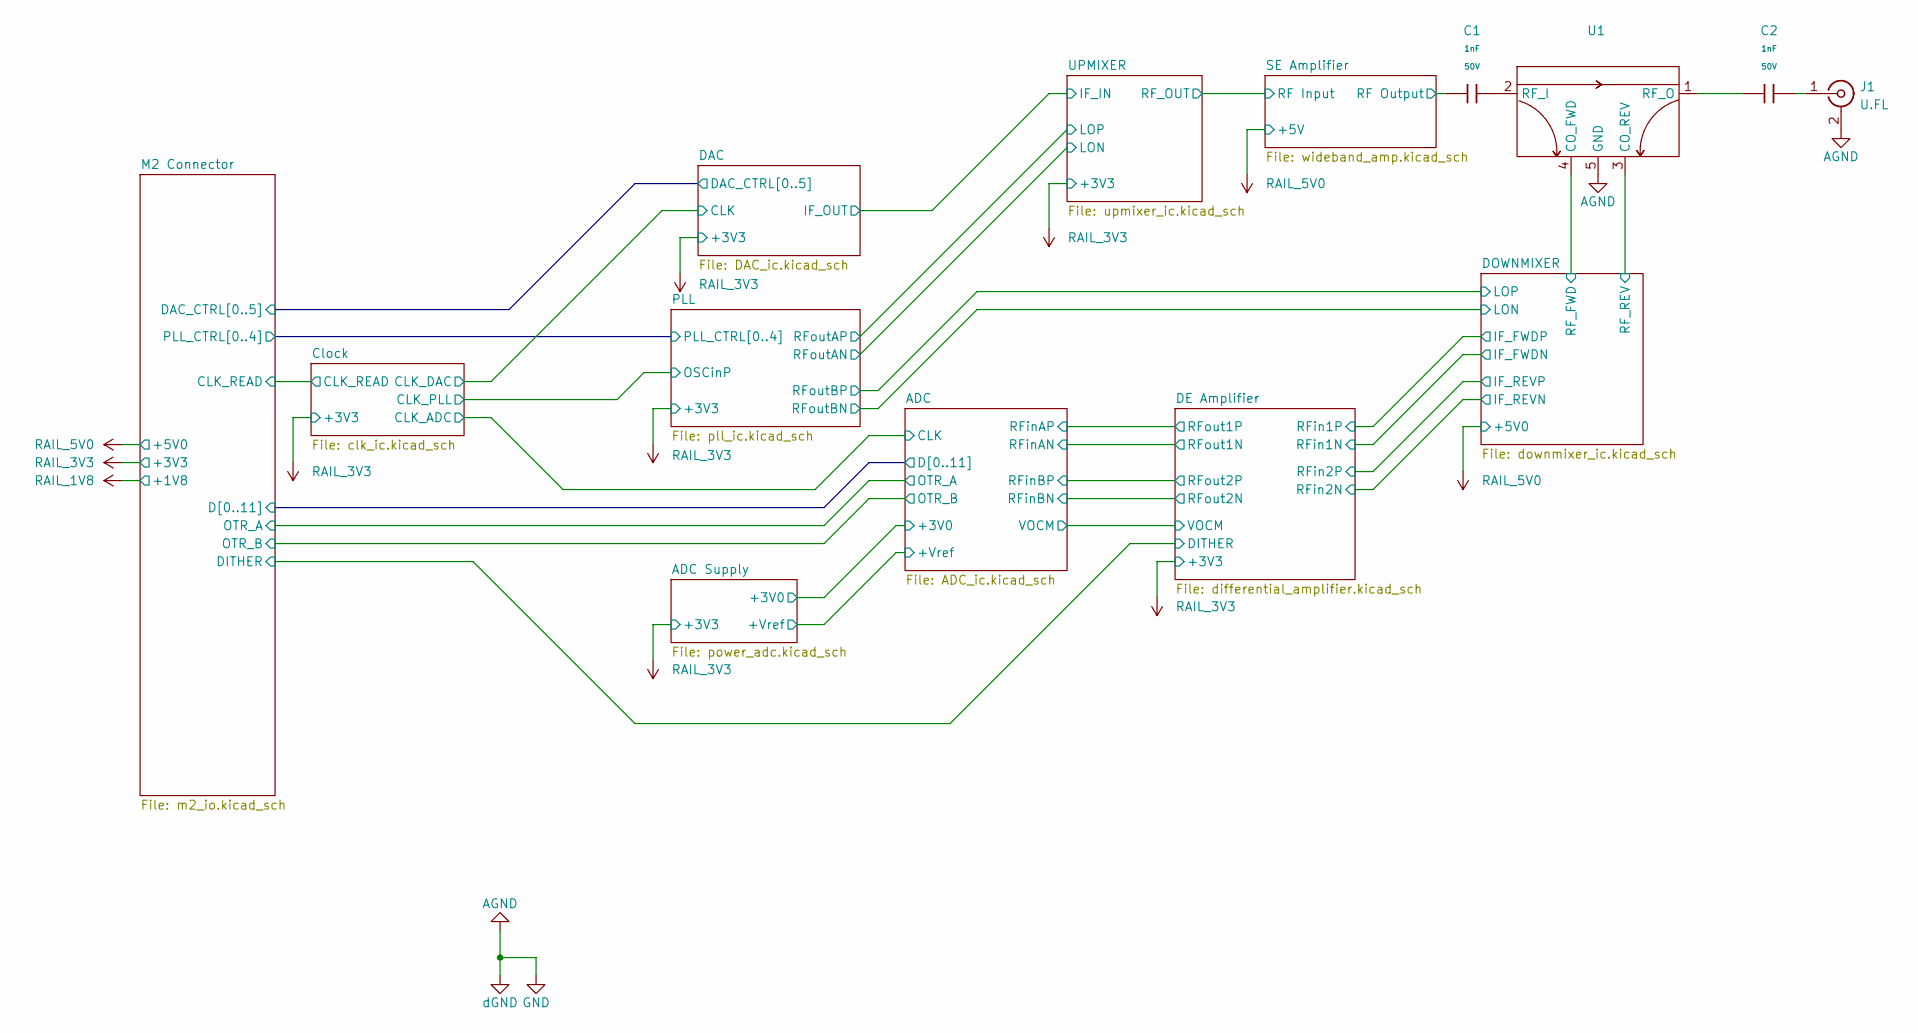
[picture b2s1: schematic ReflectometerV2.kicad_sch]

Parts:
C1, C2: 1nF; C_0402; Voltage Rated 50V; Tolerance ±10%; Part 0402B102K500NT; LCSC C1523
J1: U.FL; SMA_Amphenol_132289_EdgeMount; LCSC C5137195
U1: PL-423Q

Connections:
/DOWNMIXER/RF_FWD: U1.4 (CO_FWD); also elsewhere on the board
/DOWNMIXER/RF_REV: U1.3 (CO_REV); also elsewhere on the board
/SE Amplifier/RF Output: C1.1; also elsewhere on the board
AGND: J1.2 (Ext), U1.5 (GND); also elsewhere on the board
unnamed: C2.2, J1.1 (In)
unnamed: C1.2, U1.2 (RF_I)
unnamed: C2.1, U1.1 (RF_O)
